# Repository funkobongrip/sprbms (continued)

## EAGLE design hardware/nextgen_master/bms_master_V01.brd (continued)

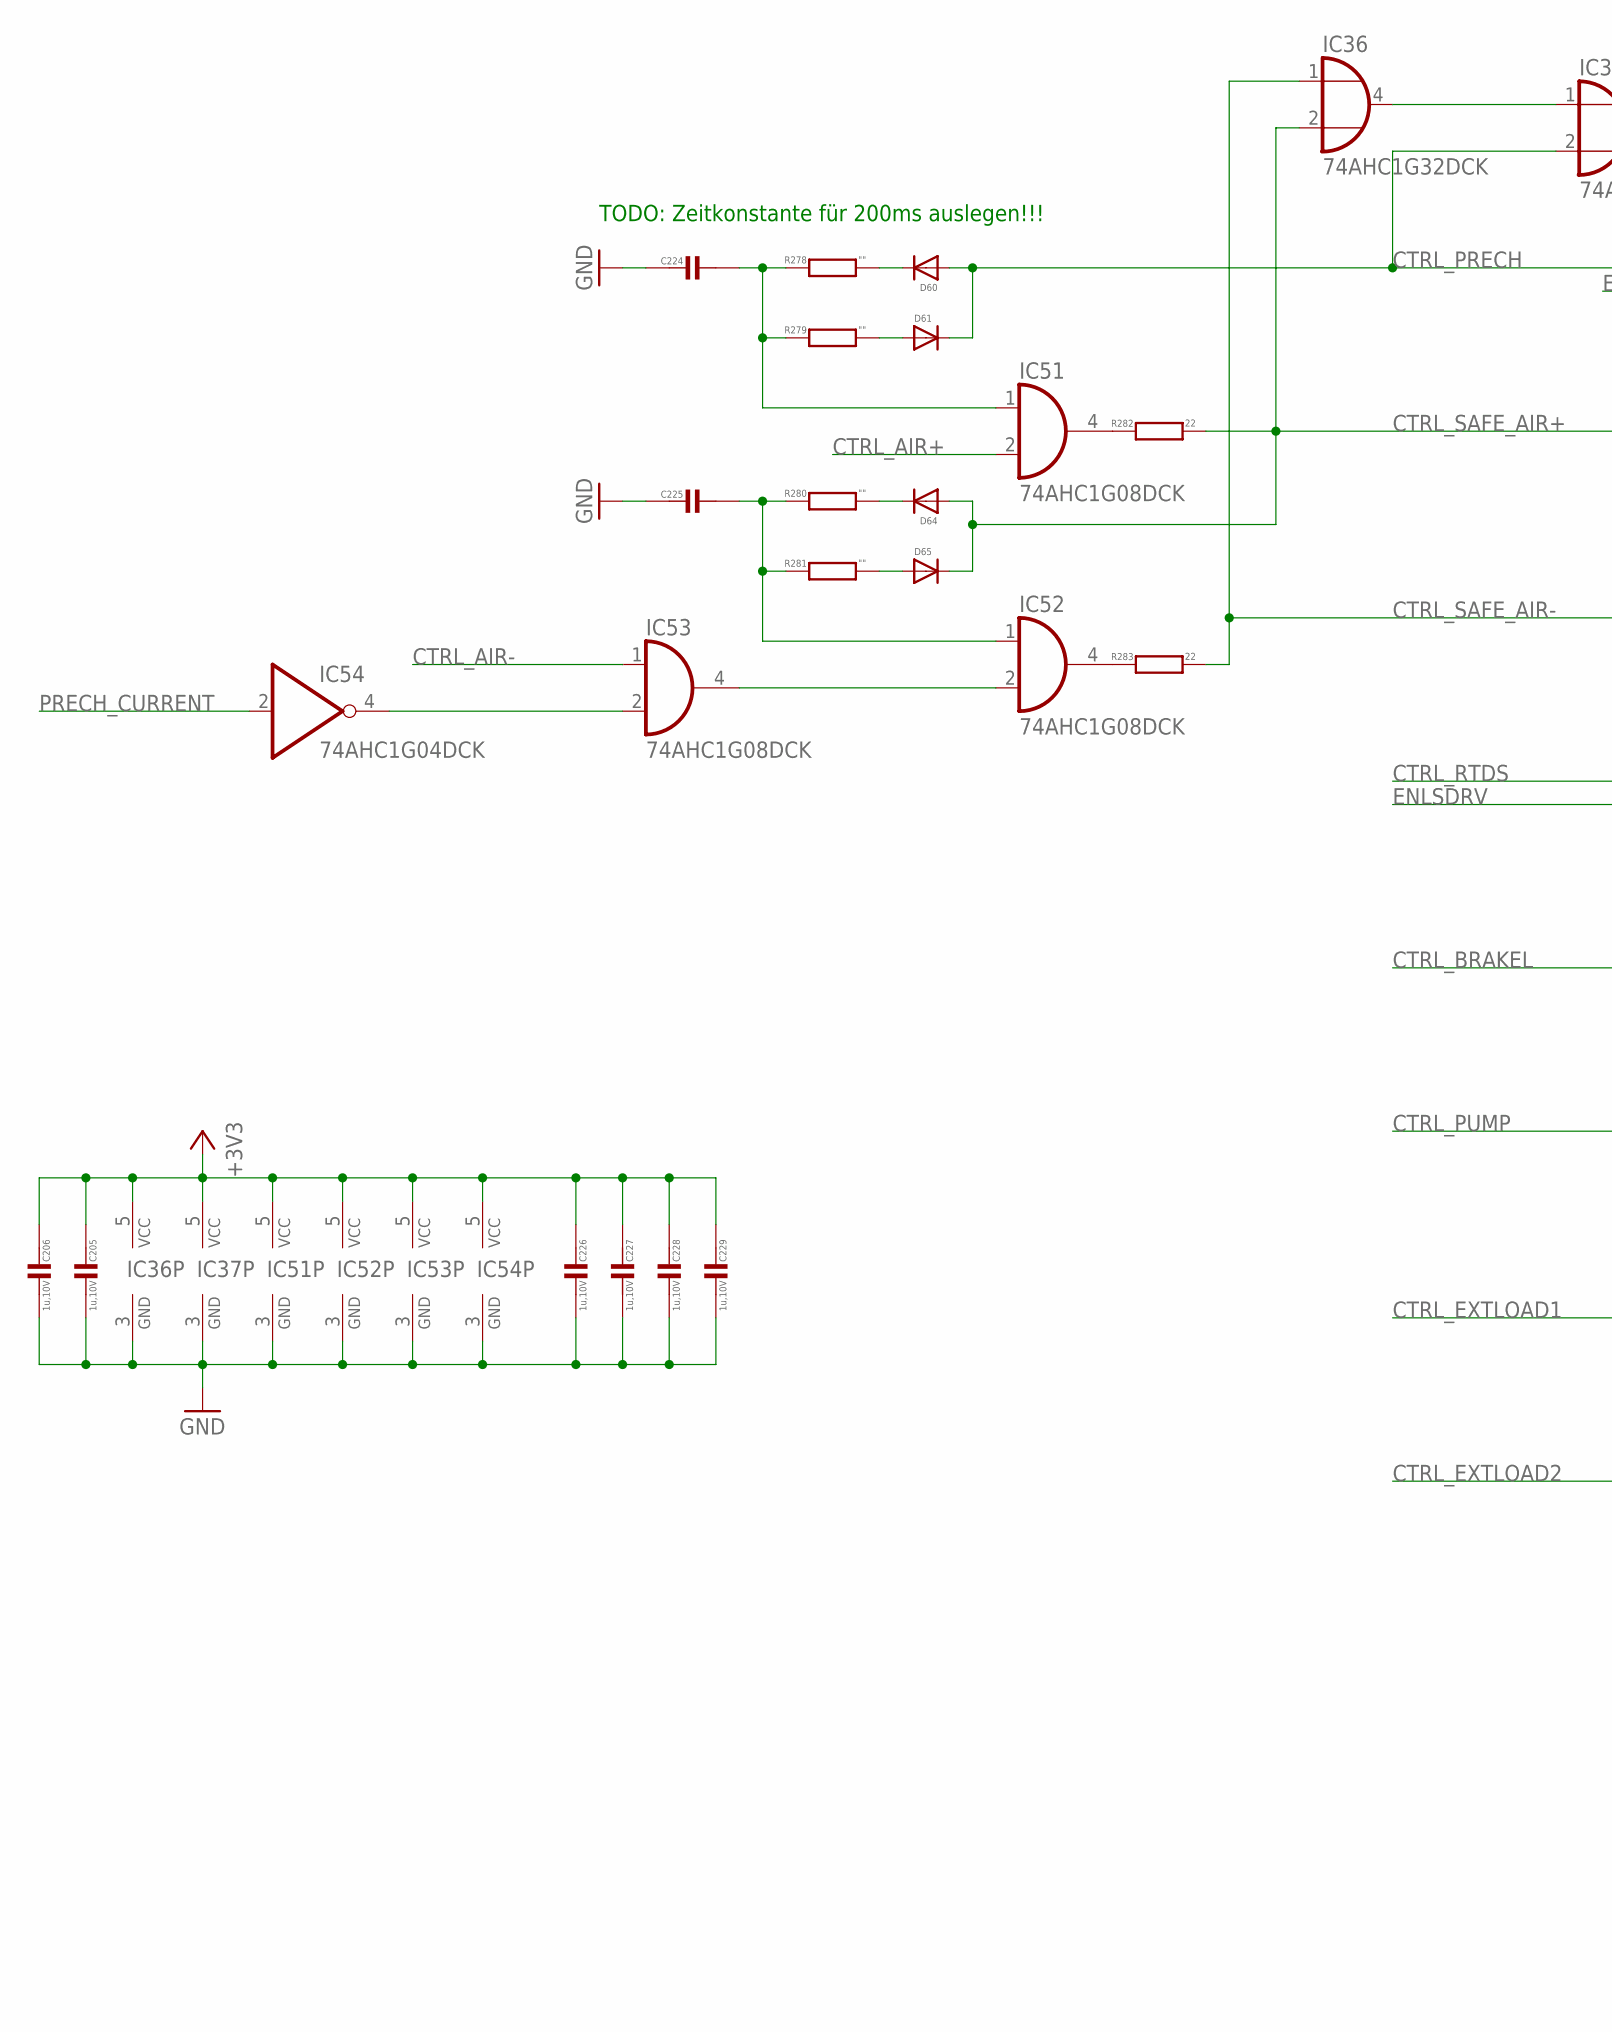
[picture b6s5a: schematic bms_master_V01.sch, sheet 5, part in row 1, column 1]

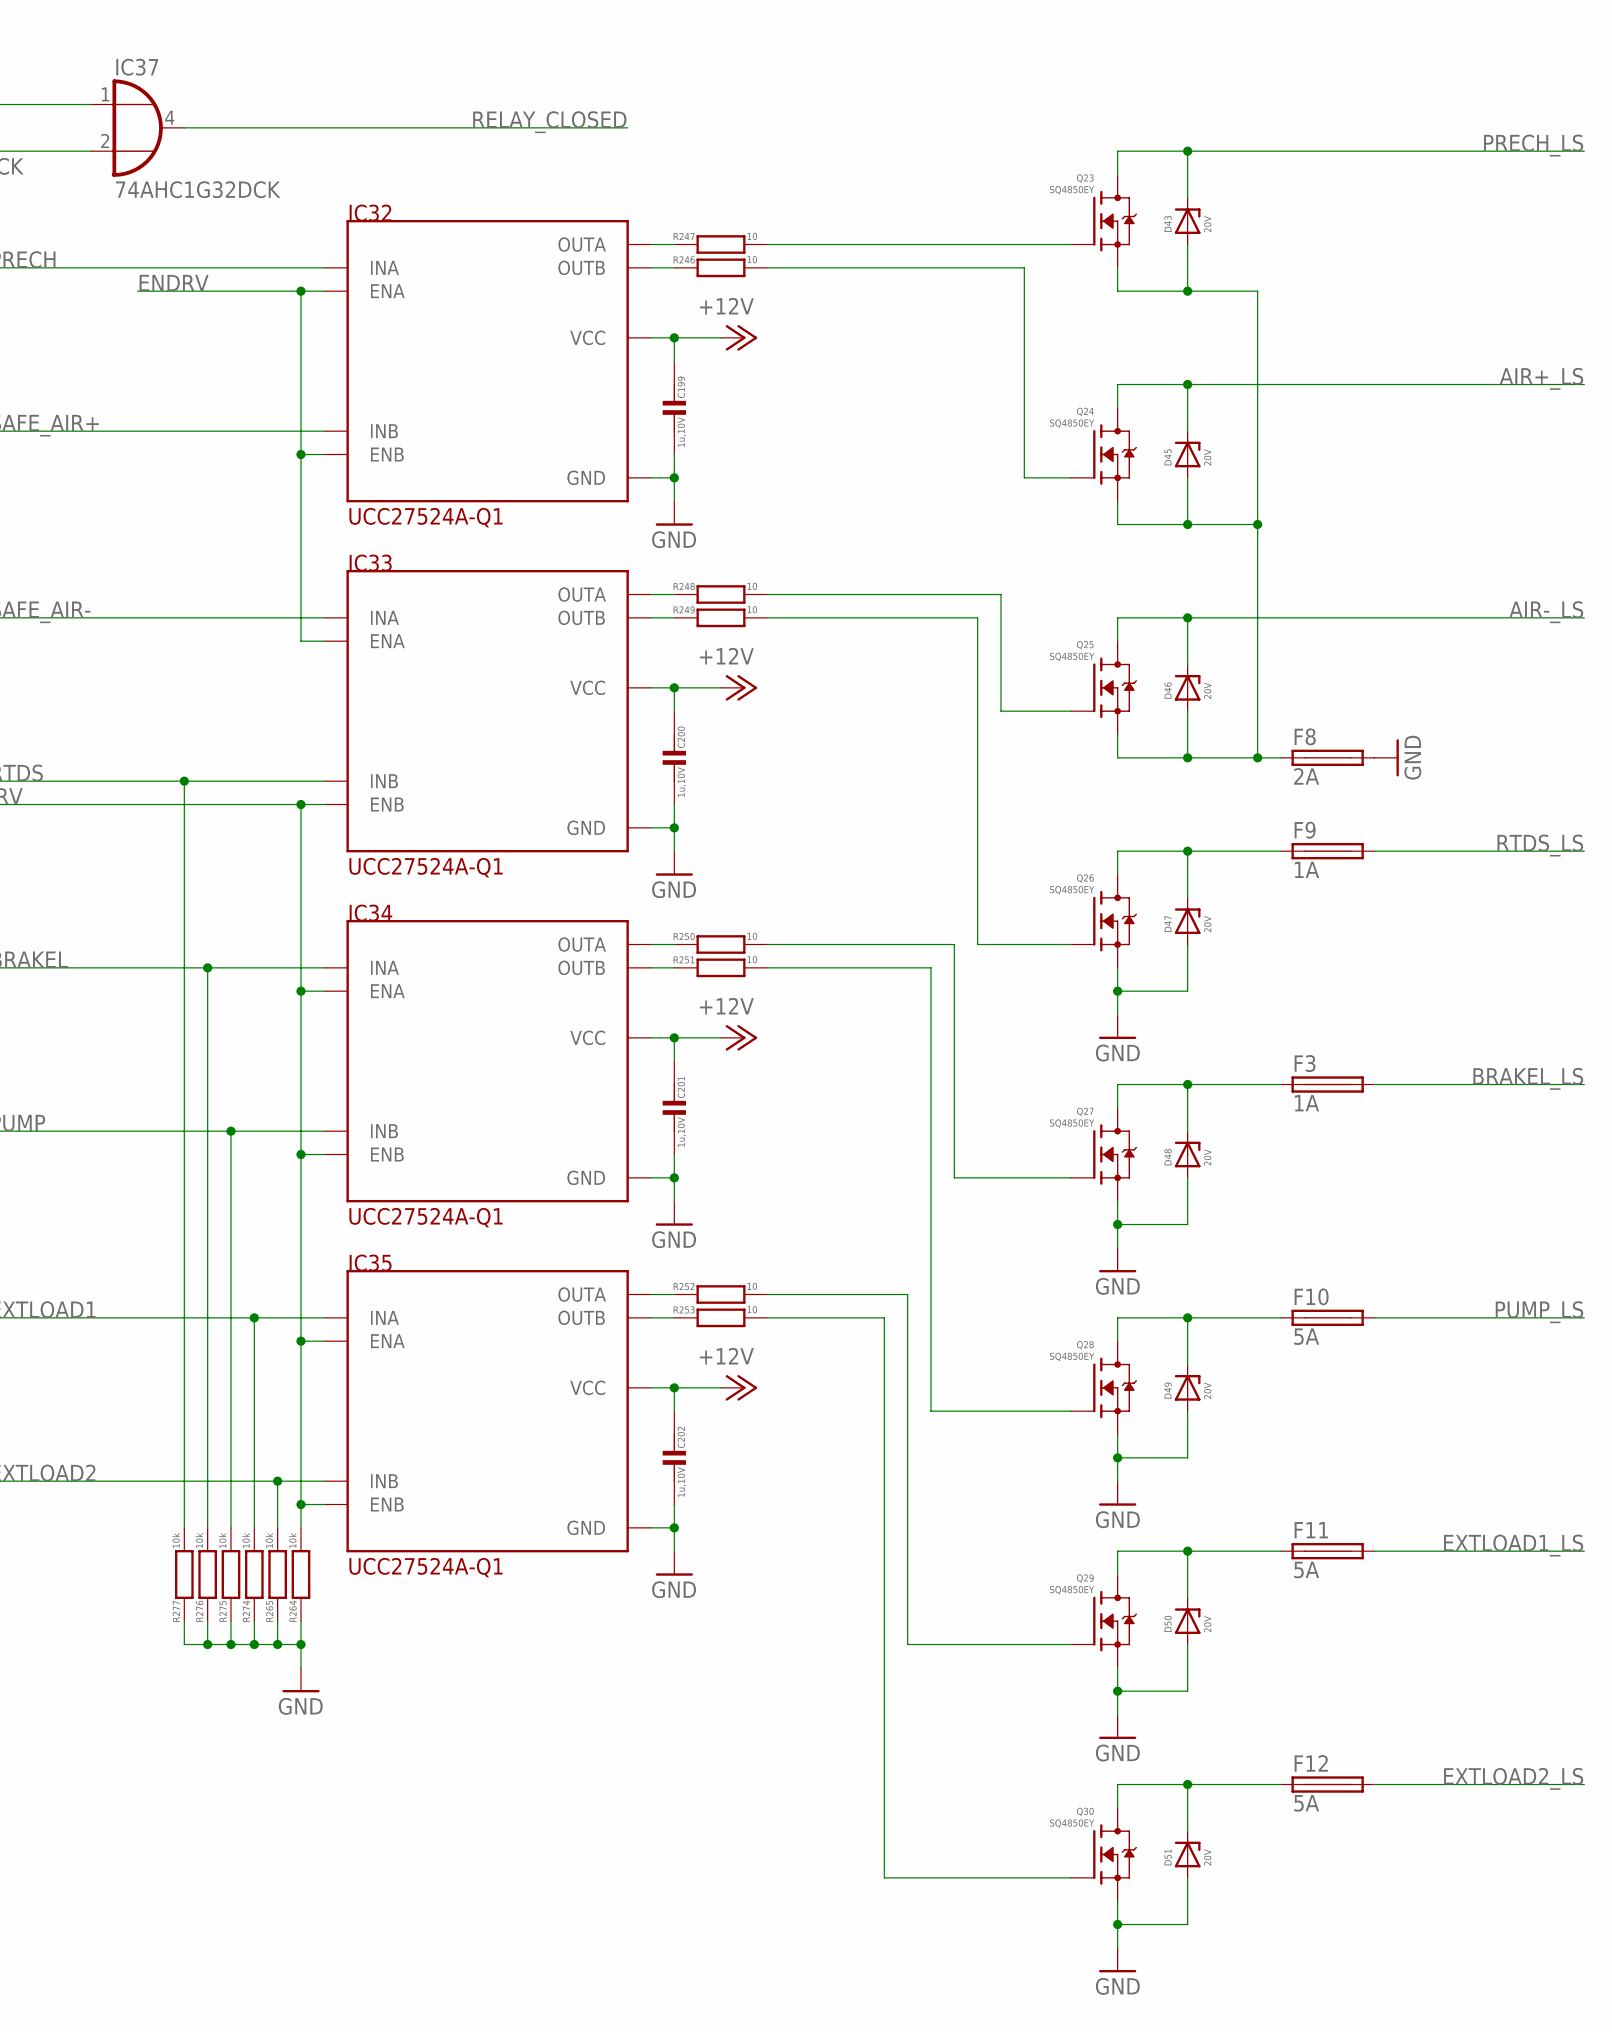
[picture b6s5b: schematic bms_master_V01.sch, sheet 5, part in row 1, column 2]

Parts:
C199, C200, C201, C202, C205, C206, C226, C227, C228, C229: 1u,10V; C0402
C224, C225: C0402
D43, D45, D46, D47, D48, D49, D50, D51: 20V; DO-214AC
D60, D61, D64, D65: DIODE-SOD523; SOD523
F3, F9: 1A; LITTLEFUSE_17867640001
F8: 2A; LITTLEFUSE_17867640001
F10, F11, F12: 5A; LITTLEFUSE_17867640001
IC32, IC33, IC34, IC35: UCC27524A-Q1; SO08
IC36, IC37: 74AHC1G32DCK; SC70-5
IC51, IC52, IC53: 74AHC1G08DCK; SC70-5
IC54: 74AHC1G04DCK; SC70-5
Q23, Q24, Q25, Q26, Q27, Q28, Q29, Q30: SQ4850EY; SO-8
R246, R247, R248, R249, R250, R251, R252, R253: 10; R1206
R264, R265, R274, R275, R276, R277: 10k; R1206
R278, R279, R280, R281: ""; R0402
R282, R283: 22; R0402

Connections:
+3V3: C205.2, C206.2, C226.2, C227.2, C228.2, C229.2, IC36.5 (VCC), IC37.5 (VCC), IC51.5 (VCC), IC52.5 (VCC), IC53.5 (VCC), IC54.5 (VCC); also elsewhere on the board
+12V: C199.2, C200.2, C201.2, C202.2, IC32.6 (VCC), IC33.6 (VCC), IC34.6 (VCC), IC35.6 (VCC); also elsewhere on the board
AIR+_LS: D45.C, Q24.5 (D), Q24.6 (D), Q24.7 (D), Q24.8 (D)
AIR-_LS: D46.C, Q25.5 (D), Q25.6 (D), Q25.7 (D), Q25.8 (D)
BRAKEL_LS: F3.2
CTRL_AIR+: IC51.2 (I1); also elsewhere on the board
CTRL_AIR-: IC53.1 (I0); also elsewhere on the board
CTRL_BRAKEL: IC34.2 (INA), R276.2; also elsewhere on the board
CTRL_EXTLOAD1: IC35.2 (INA), R274.2; also elsewhere on the board
CTRL_EXTLOAD2: IC35.4 (INB), R265.2; also elsewhere on the board
CTRL_PRECH: D60.A, D61.C, IC32.2 (INA), IC37.2 (I1); also elsewhere on the board
CTRL_PUMP: IC34.4 (INB), R275.2; also elsewhere on the board
CTRL_RTDS: IC33.4 (INB), R277.2; also elsewhere on the board
CTRL_SAFE_AIR+: D64.A, D65.C, IC32.4 (INB), IC36.2 (I1), R282.2; also elsewhere on the board
CTRL_SAFE_AIR-: IC33.2 (INA), IC36.1 (I0), R283.2; also elsewhere on the board
ENDRV: IC32.1 (ENA), IC32.8 (ENB), IC33.1 (ENA); also elsewhere on the board
ENLSDRV: IC33.8 (ENB), IC34.1 (ENA), IC34.8 (ENB), IC35.1 (ENA), IC35.8 (ENB), R264.2; also elsewhere on the board
EXTLOAD1_LS: F11.2
EXTLOAD2_LS: F12.2
GND: C199.1, C200.1, C201.1, C202.1, C205.1, C206.1, C224.2, C225.2, C226.1, C227.1, C228.1, C229.1, D47.A, D48.A, D49.A, D50.A, D51.A, F8.2, IC32.3 (GND), IC33.3 (GND), IC34.3 (GND), IC35.3 (GND), IC36.3 (GND), IC37.3 (GND), IC51.3 (GND), IC52.3 (GND), IC53.3 (GND), IC54.3 (GND), Q26.1 (S), Q26.2 (S), Q26.3 (S), Q27.1 (S), Q27.2 (S), Q27.3 (S), Q28.1 (S), Q28.2 (S), Q28.3 (S), Q29.1 (S), Q29.2 (S), Q29.3 (S), Q30.1 (S), Q30.2 (S), Q30.3 (S), R264.1, R265.1, R274.1, R275.1, R276.1, R277.1; also elsewhere on the board
unnamed: IC32.7 (OUTA), R247.1
unnamed: IC32.5 (OUTB), R246.1
unnamed: IC33.7 (OUTA), R248.1
unnamed: IC33.5 (OUTB), R249.1
unnamed: IC34.7 (OUTA), R250.1
unnamed: IC34.5 (OUTB), R251.1
unnamed: IC35.7 (OUTA), R252.1
unnamed: IC35.5 (OUTB), R253.1
unnamed: Q23.4 (G), R247.2
unnamed: Q24.4 (G), R246.2
unnamed: Q25.4 (G), R248.2
unnamed: Q26.4 (G), R249.2
unnamed: Q27.4 (G), R250.2
unnamed: Q28.4 (G), R251.2
unnamed: Q29.4 (G), R252.2
unnamed: Q30.4 (G), R253.2
unnamed: D51.C, F12.1, Q30.5 (D), Q30.6 (D), Q30.7 (D), Q30.8 (D)
unnamed: D50.C, F11.1, Q29.5 (D), Q29.6 (D), Q29.7 (D), Q29.8 (D)
unnamed: D49.C, F10.1, Q28.5 (D), Q28.6 (D), Q28.7 (D), Q28.8 (D)
unnamed: D47.C, F9.1, Q26.5 (D), Q26.6 (D), Q26.7 (D), Q26.8 (D)
unnamed: D48.C, F3.1, Q27.5 (D), Q27.6 (D), Q27.7 (D), Q27.8 (D)
unnamed: IC36.4 (O), IC37.1 (I0)
unnamed: D61.A, R279.2
unnamed: D60.C, R278.2
unnamed: C224.1, IC51.1 (I0), R278.1, R279.1
unnamed: D65.A, R281.2
unnamed: D64.C, R280.2
unnamed: C225.1, IC52.1 (I0), R280.1, R281.1
unnamed: IC52.2 (I1), IC53.4 (O)
unnamed: IC53.2 (I1), IC54.4 (O)
unnamed: IC51.4 (O), R282.1
unnamed: IC52.4 (O), R283.1
PRECH_CURRENT: IC54.2 (I); also elsewhere on the board
PRECH_LS: D43.C, Q23.5 (D), Q23.6 (D), Q23.7 (D), Q23.8 (D)
PUMP_LS: F10.2
RELAY_CLOSED: IC37.4 (O); also elsewhere on the board
RELAY_GND: D43.A, D45.A, D46.A, F8.1, Q23.1 (S), Q23.2 (S), Q23.3 (S), Q24.1 (S), Q24.2 (S), Q24.3 (S), Q25.1 (S), Q25.2 (S), Q25.3 (S)
RTDS_LS: F9.2

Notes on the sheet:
TODO: Zeitkonstante für 200ms auslegen!!!

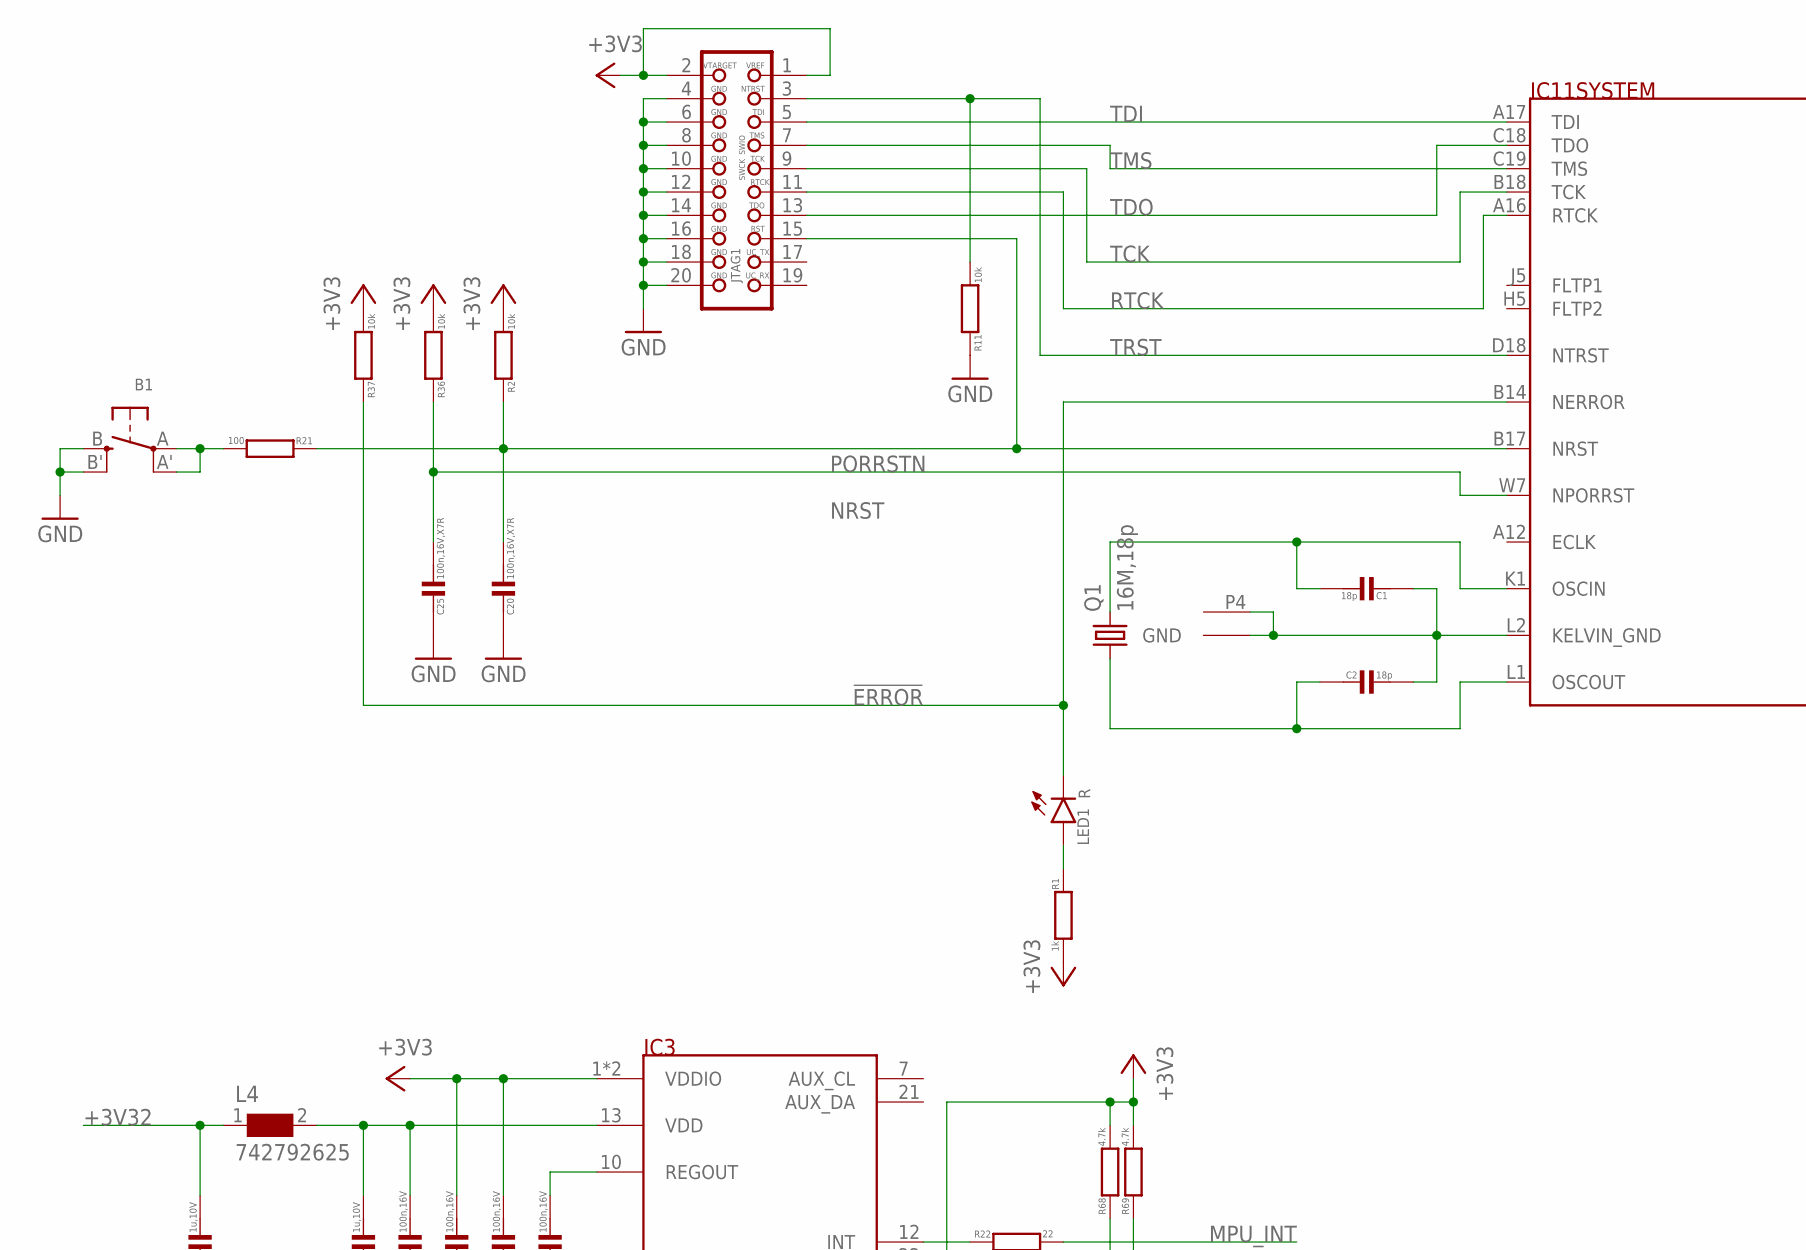
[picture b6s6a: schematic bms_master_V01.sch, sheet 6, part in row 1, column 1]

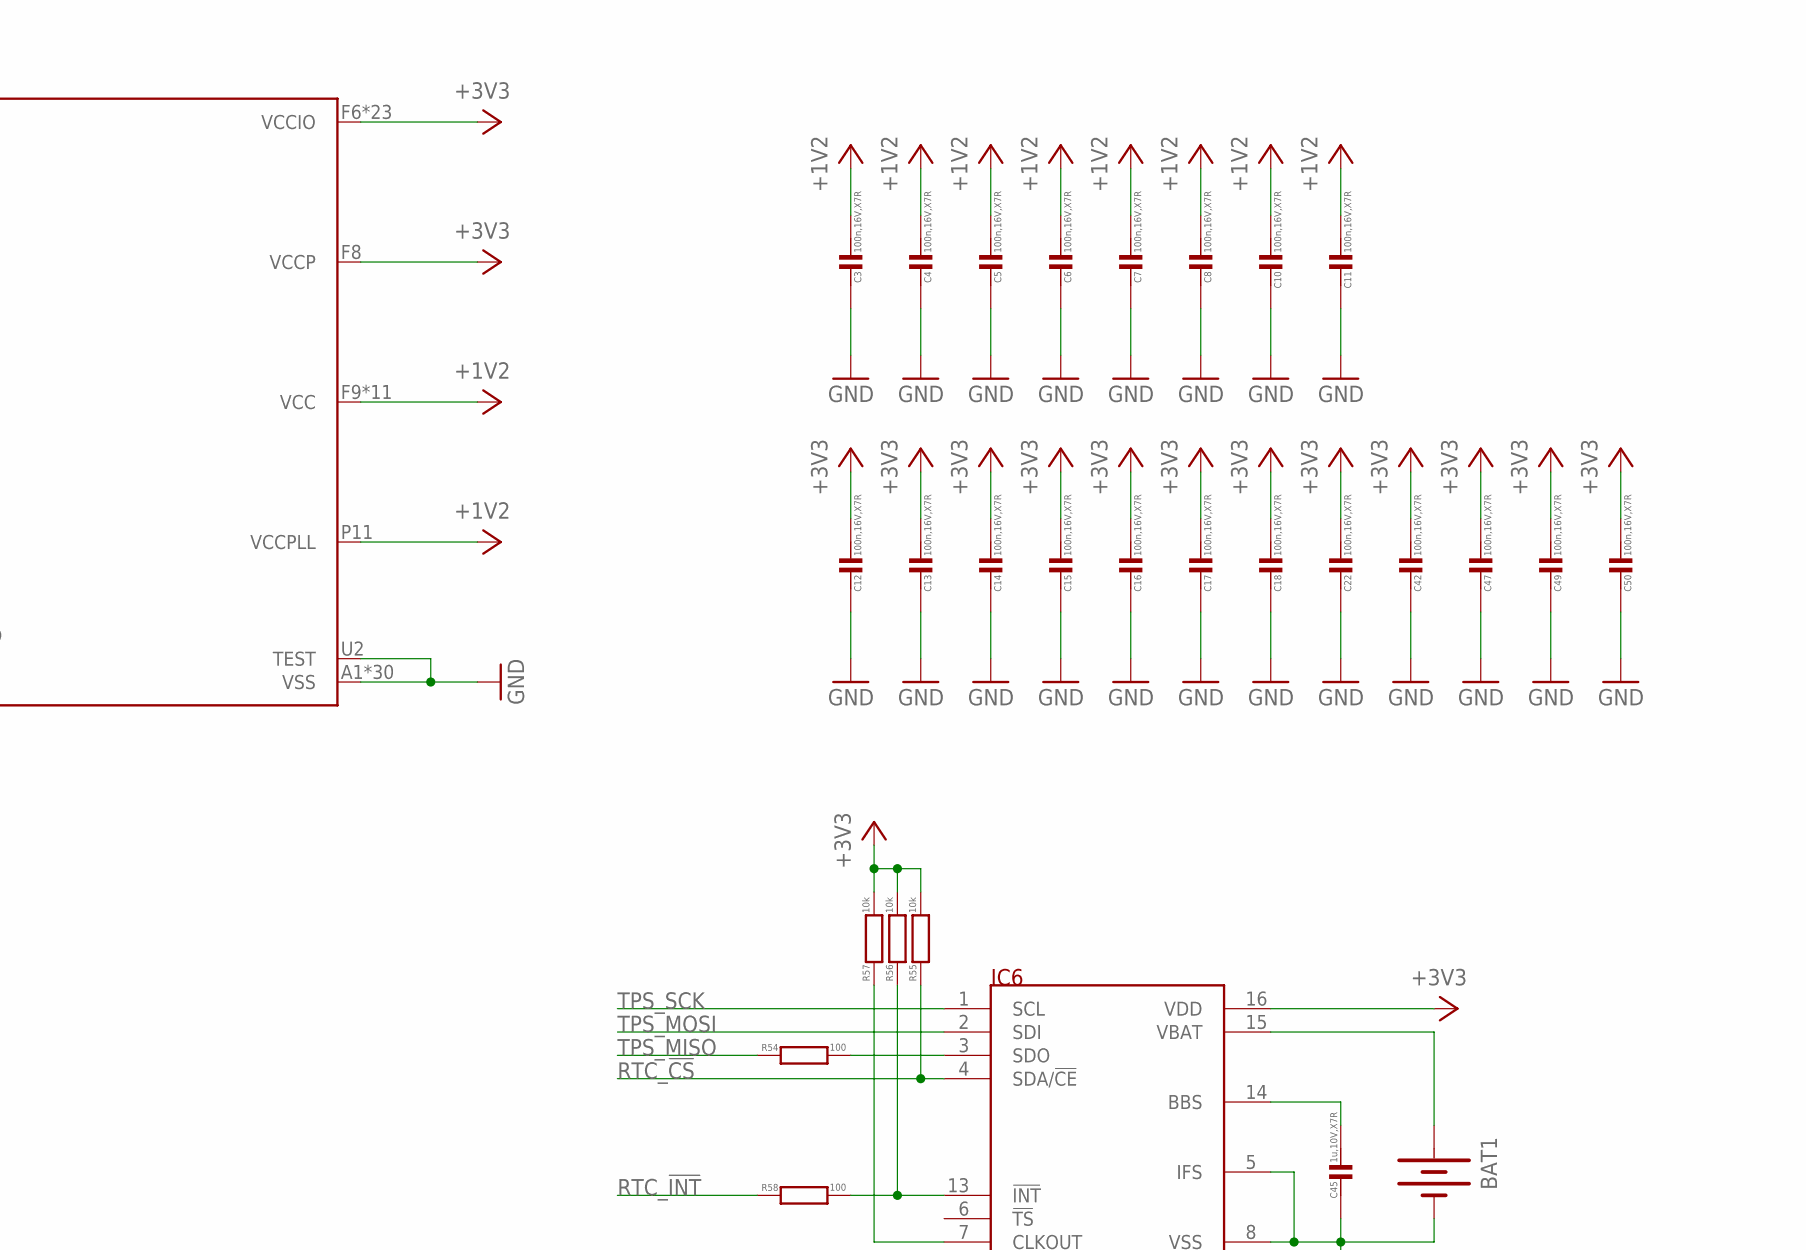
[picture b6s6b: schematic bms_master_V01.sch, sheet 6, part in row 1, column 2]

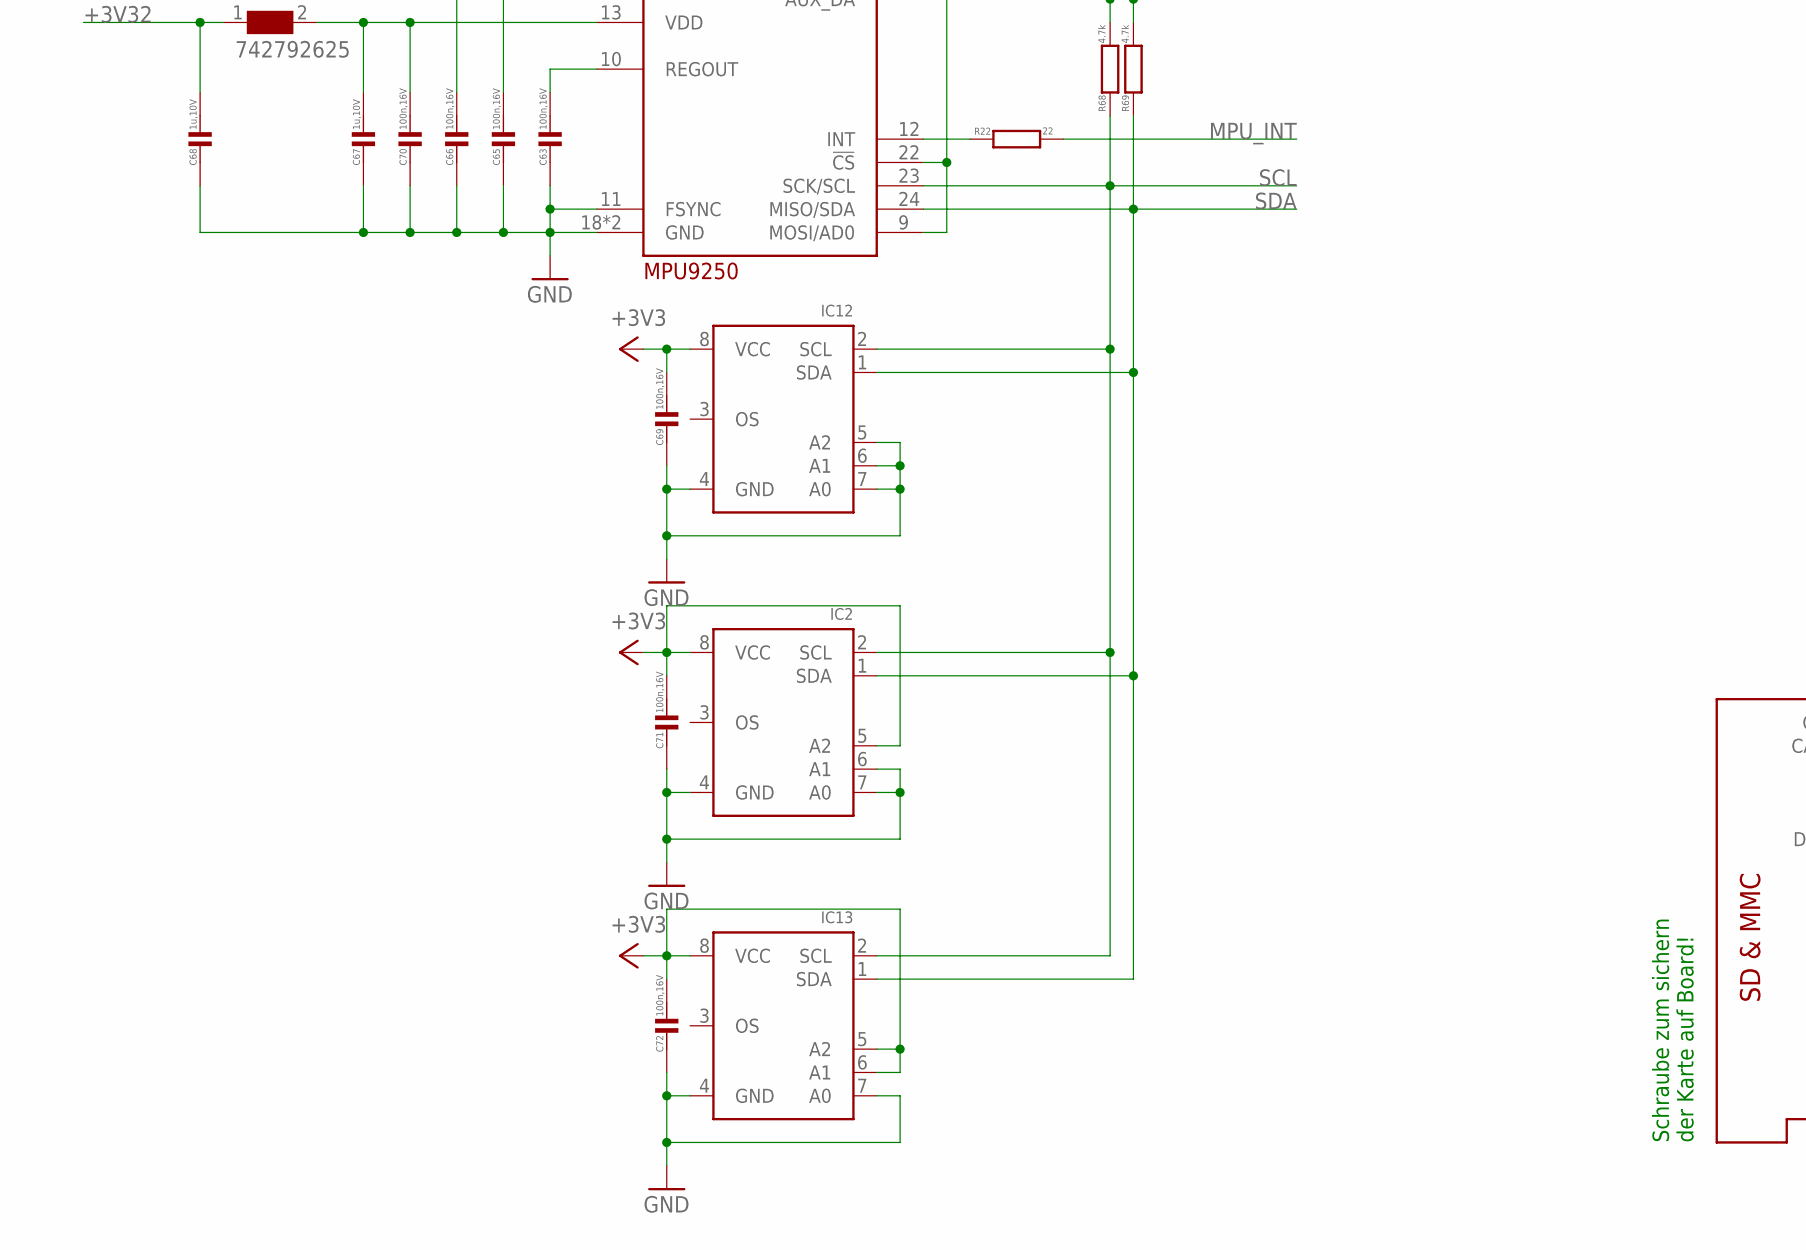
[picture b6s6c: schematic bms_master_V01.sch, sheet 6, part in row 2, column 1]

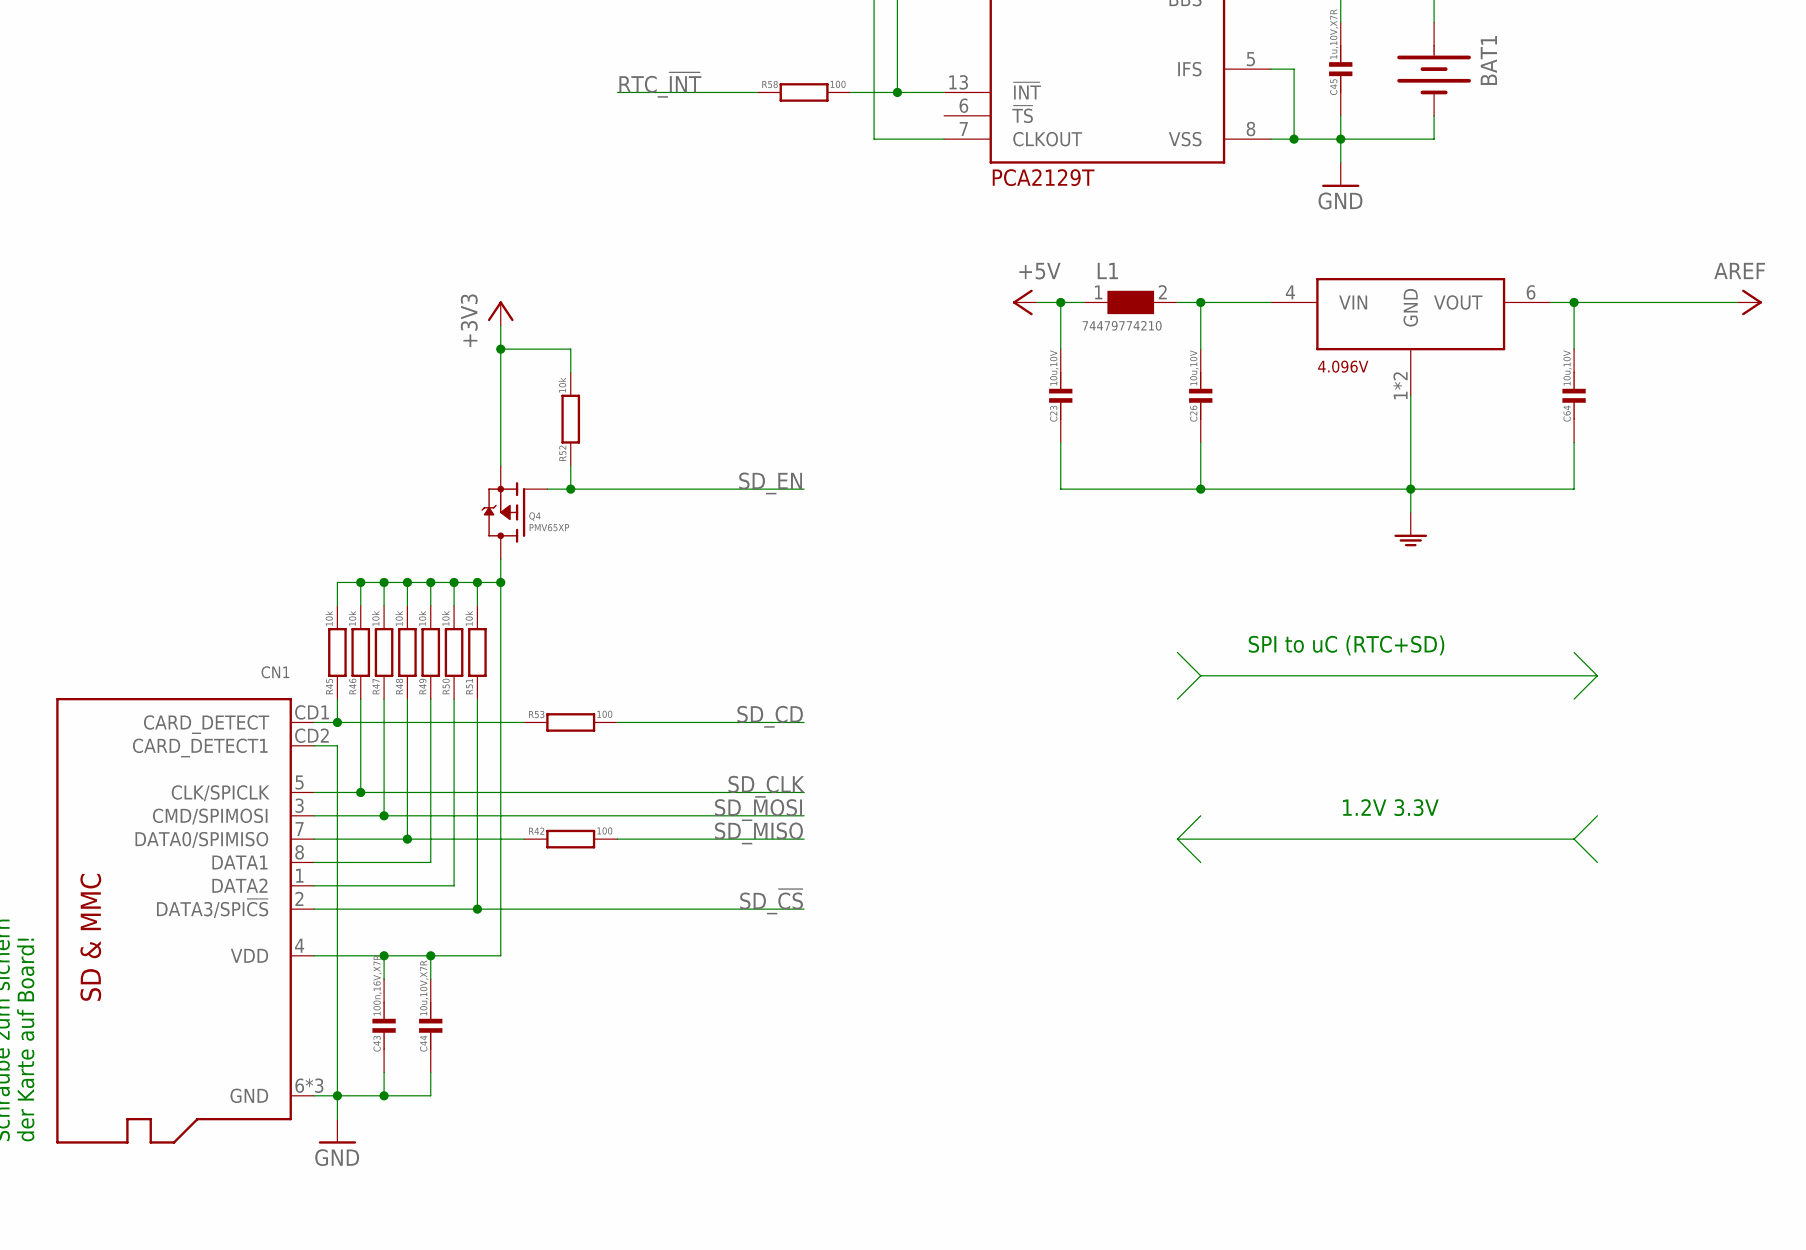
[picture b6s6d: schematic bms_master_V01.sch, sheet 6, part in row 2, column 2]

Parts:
B1: SWITCH_TACT_SMT4.6X2.8; BTN_KMR2_4.6X2.8
BAT1: BATTERY20PTH; BATTCOM_20MM_PTH
C1, C2: 18p; C0402
C3, C4, C5, C6, C7, C8, C10, C11, C12, C13, C14, C15, C16, C17, C18, C20, C22, C25, C42, C43, C47, C49, C50: 100n,16V,X7R; C0402
C23, C26, C64: 10u,10V; C0603
C44: 10u,10V,X7R; C0603
C45: 1u,10V,X7R; C0402
C63, C65, C66, C69, C70, C71, C72: 100n,16V; C0402
C67, C68: 1u,10V; C0402
CN1: MICROSD_3M; MICROSD
IC2, IC12, IC13: TEMP_LM75B; TSSOP8
IC3: MPU9250; QFN-24-NP
IC6: PCA2129T; SO16W
IC11: TMS570LS3137ZWT; S-PBGA-N337
JTAG1: JTAG20-SMT1.27; 2X10_1.27MM_SMT
L1: 74479774210; WE-PMI_0805
L4: 742792625; 0603
LED1: R; CHIPLED_0603
Q1: 16M,18p; MT
Q4: PMV65XP; SOT23
R1: 1k; R0402
R2, R11, R36, R37, R45, R46, R47, R48, R49, R50, R51, R52, R55, R56, R57: 10k; R0402
R21, R42, R53, R54, R58: 100; R0402
R22: 22; R0402
R68, R69: 4.7k; R0402
U$23: 4.096V; SOT23-6

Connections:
5VFILT: C26.1, L1.2, U$23.4 (VIN)
!ERROR: IC11.B14 (NERROR), LED1.C, R37.1; also elsewhere on the board
!INT_OUT: IC6.13 (!INT), R56.1, R58.2
+1V2: C3.1, C4.1, C5.1, C6.1, C7.1, C8.1, C10.1, C11.1, IC11.F9 (VCC), IC11.F10 (VCC), IC11.H10 (VCC), IC11.J14 (VCC), IC11.K6 (VCC), IC11.K8 (VCC), IC11.K12 (VCC), IC11.K14 (VCC), IC11.L6 (VCC), IC11.M10 (VCC), IC11.P10 (VCC), IC11.P11 (VCCPLL); also elsewhere on the board
+3V3: C12.1, C13.1, C14.1, C15.1, C16.1, C17.1, C18.1, C22.1, C42.1, C47.1, C49.1, C50.1, C65.1, C66.1, C69.1, C71.1, C72.1, IC2.5 (A2), IC2.8 (VCC), IC3.1 (VDDIO), IC3.8 (VDDIO), IC3.9 (MOSI/AD0), IC3.22 (!CS), IC6.16 (VDD), IC11.F6 (VCCIO), IC11.F7 (VCCIO), IC11.F8 (VCCP), IC11.F11 (VCCIO), IC11.F12 (VCCIO), IC11.F13 (VCCIO), IC11.F14 (VCCIO), IC11.G6 (VCCIO), IC11.G14 (VCCIO), IC11.H6 (VCCIO), IC11.H14 (VCCIO), IC11.J6 (VCCIO), IC11.L14 (VCCIO), IC11.M6 (VCCIO), IC11.M14 (VCCIO), IC11.N6 (VCCIO), IC11.N14 (VCCIO), IC11.P6 (VCCIO), IC11.P7 (VCCIO), IC11.P8 (VCCIO), IC11.P9 (VCCIO), IC11.P12 (VCCIO), IC11.P13 (VCCIO), IC11.P14 (VCCIO), IC12.8 (VCC), IC13.5 (A2), IC13.6 (A1), IC13.8 (VCC), JTAG1.1, JTAG1.2, Q4.2 (S), R1.2, R2.2, R36.2, R37.2, R52.2, R55.2, R56.2, R57.2, R68.2, R69.2; also elsewhere on the board
+3V32: C68.1, L4.1; also elsewhere on the board
+5V: C23.1, L1.1; also elsewhere on the board
AGND: C23.2, C26.2, C64.2, U$23.1 (GND), U$23.2 (GND); also elsewhere on the board
AREF: C64.1, U$23.6 (VOUT); also elsewhere on the board
BBS: C45.1, IC6.14 (BBS)
CLKOUTOUT: IC6.7 (CLKOUT), R57.1
GND: B1.B (S), B1.B' (S1), BAT1.2 (-), C3.2, C4.2, C5.2, C6.2, C7.2, C8.2, C10.2, C11.2, C12.2, C13.2, C14.2, C15.2, C16.2, C17.2, C18.2, C20.2, C22.2, C25.2, C42.2, C43.2, C44.2, C45.2, C47.2, C49.2, C50.2, C63.2, C65.2, C66.2, C67.2, C68.2, C69.2, C70.2, C71.2, C72.2, CN1.6 (GND), CN1.CD2 (CARD_DETECT1), CN1.MT1 (GND), CN1.MT2 (GND), IC2.4 (GND), IC2.6 (A1), IC2.7 (A0), IC3.11 (FSYNC), IC3.18 (GND), IC3.20 (GND), IC6.5 (IFS), IC6.8 (VSS), IC11.A1 (VSS), IC11.A2 (VSS), IC11.A18 (VSS), IC11.A19 (VSS), IC11.B1 (VSS), IC11.B19 (VSS), IC11.H8 (VSS), IC11.H9 (VSS), IC11.H11 (VSS), IC11.H12 (VSS), IC11.J8 (VSS), IC11.J9 (VSS), IC11.J10 (VSS), IC11.J11 (VSS), IC11.J12 (VSS), IC11.K9 (VSS), IC11.K10 (VSS), IC11.K11 (VSS), IC11.L8 (VSS), IC11.L9 (VSS), IC11.L10 (VSS), IC11.L11 (VSS), IC11.L12 (VSS), IC11.M8 (VSS), IC11.M9 (VSS), IC11.M11 (VSS), IC11.M12 (VSS), IC11.U2 (TEST), IC11.V1 (VSS), IC11.W1 (VSS), IC11.W2 (VSS), IC12.4 (GND), IC12.5 (A2), IC12.6 (A1), IC12.7 (A0), IC13.4 (GND), IC13.7 (A0), JTAG1.4, JTAG1.6, JTAG1.8, JTAG1.10, JTAG1.12, JTAG1.14, JTAG1.16, JTAG1.18, JTAG1.20, R11.1; also elsewhere on the board
KGND: C1.2, C2.1, IC11.L2 (KELVIN_GND), Q1.P2 (GND), Q1.P4 (GND1)
LED1A: LED1.A, R1.1
MPUVCC: C67.1, C70.1, IC3.13 (VDD), L4.2
MPU_INT: R22.2
unnamed: IC3.12 (INT), R22.1
NRST: C20.1, IC11.B17 (NRST), JTAG1.15, R2.1, R21.1
NRSTBTN: B1.A, B1.A' (P1), R21.2
OSCIN: C1.1, IC11.K1 (OSCIN), Q1.P3 (2)
OSCOUT: C2.2, IC11.L1 (OSCOUT), Q1.P1 (1)
PORRSTN: C25.1, IC11.W7 (NPORRST), R36.1; also elsewhere on the board
REGOUT: C63.1, IC3.10 (REGOUT)
RTCK: IC11.A16 (RTCK), JTAG1.11
RTC_!CS: IC6.4 (SDA/!CE), R55.1; also elsewhere on the board
RTC_!INT: R58.1; also elsewhere on the board
RTC_SDO: IC6.3 (SDO), R54.2
SCL: IC2.2 (SCL), IC3.23 (SCK/SCL), IC12.2 (SCL), IC13.2 (SCL), R68.1; also elsewhere on the board
SD1_D2: CN1.1 (DATA2), R50.1
SDA: IC2.1 (SDA), IC3.24 (MISO/SDA), IC12.1 (SDA), IC13.1 (SDA), R69.1; also elsewhere on the board
SD_!CS: CN1.2 (DATA3/SPI!CS), R51.1; also elsewhere on the board
SD_+3V3: C43.1, C44.1, CN1.4 (VDD), Q4.3 (D), R45.2, R46.2, R47.2, R48.2, R49.2, R50.2, R51.2
SD_CD: R53.2; also elsewhere on the board
SD_CDOUT: CN1.CD1 (CARD_DETECT), R45.1, R53.1
SD_CLK: CN1.5 (CLK/SPICLK), R46.1; also elsewhere on the board
SD_D1: CN1.8 (DATA1), R49.1
SD_EN: Q4.1 (G), R52.1; also elsewhere on the board
SD_MISO: R42.2; also elsewhere on the board
SD_MOSI: CN1.3 (CMD/SPIMOSI), R47.1; also elsewhere on the board
SD_SDO_OUT: CN1.7 (DATA0/SPIMISO), R42.1, R48.1
TCK: IC11.B18 (TCK), JTAG1.9
TDI: IC11.A17 (TDI), JTAG1.5
TDO: IC11.C18 (TDO), JTAG1.13
TMS: IC11.C19 (TMS), JTAG1.7
TPS_MISO: R54.1; also elsewhere on the board
TPS_MOSI: IC6.2 (SDI); also elsewhere on the board
TPS_SCK: IC6.1 (SCL); also elsewhere on the board
TRST: IC11.D18 (NTRST), JTAG1.3, R11.2
VBAT: BAT1.1 (+), IC6.15 (VBAT)

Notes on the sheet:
Schraube zum sichern der Karte auf Board!
SPI to uC (RTC+SD)
1.2V 3.3V
